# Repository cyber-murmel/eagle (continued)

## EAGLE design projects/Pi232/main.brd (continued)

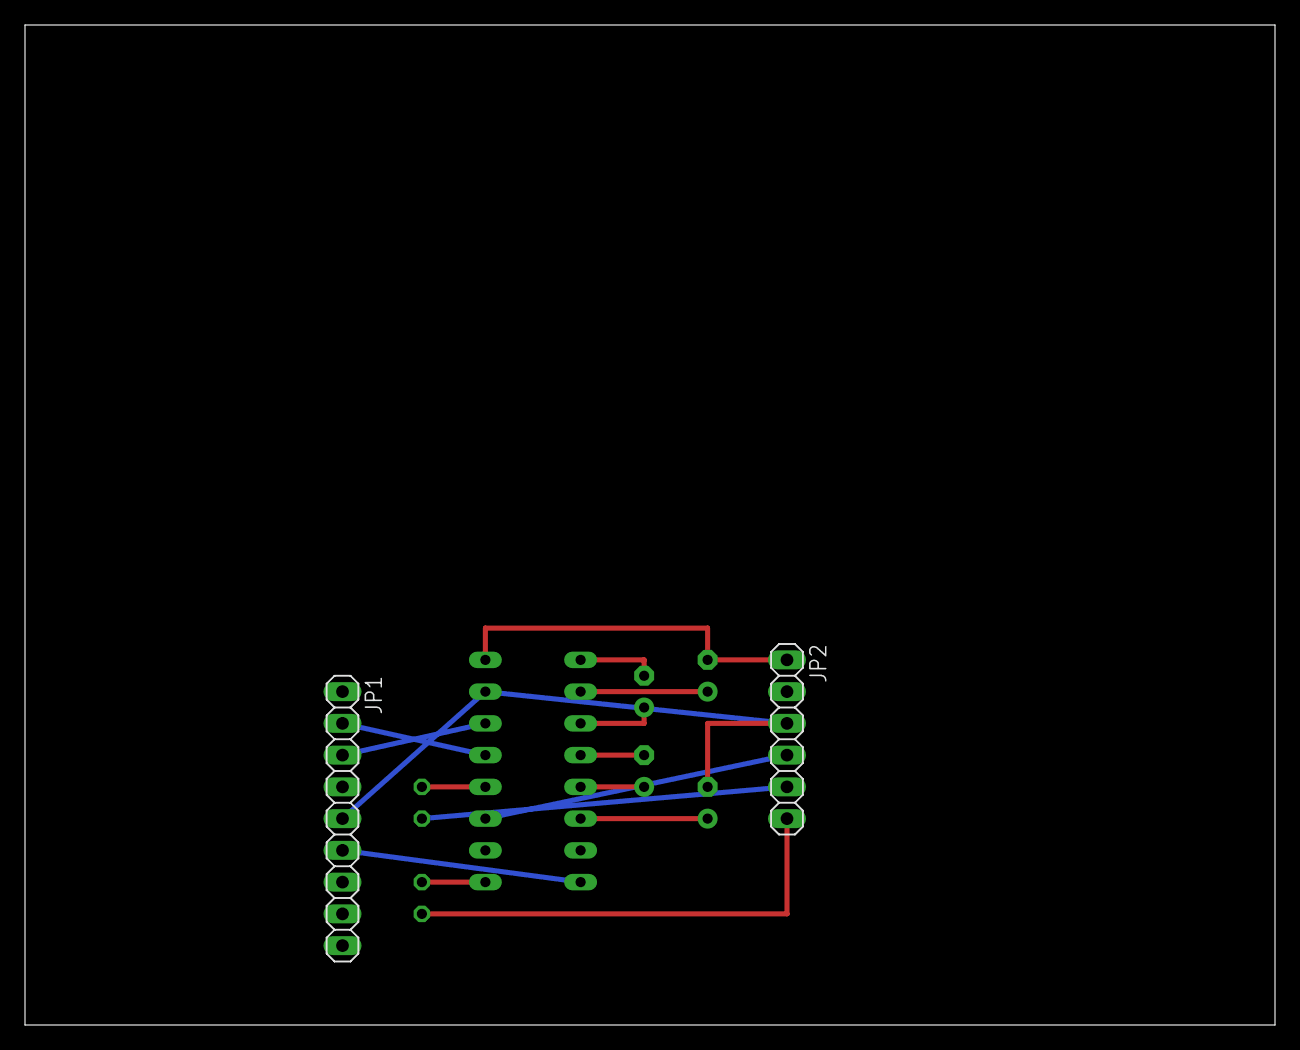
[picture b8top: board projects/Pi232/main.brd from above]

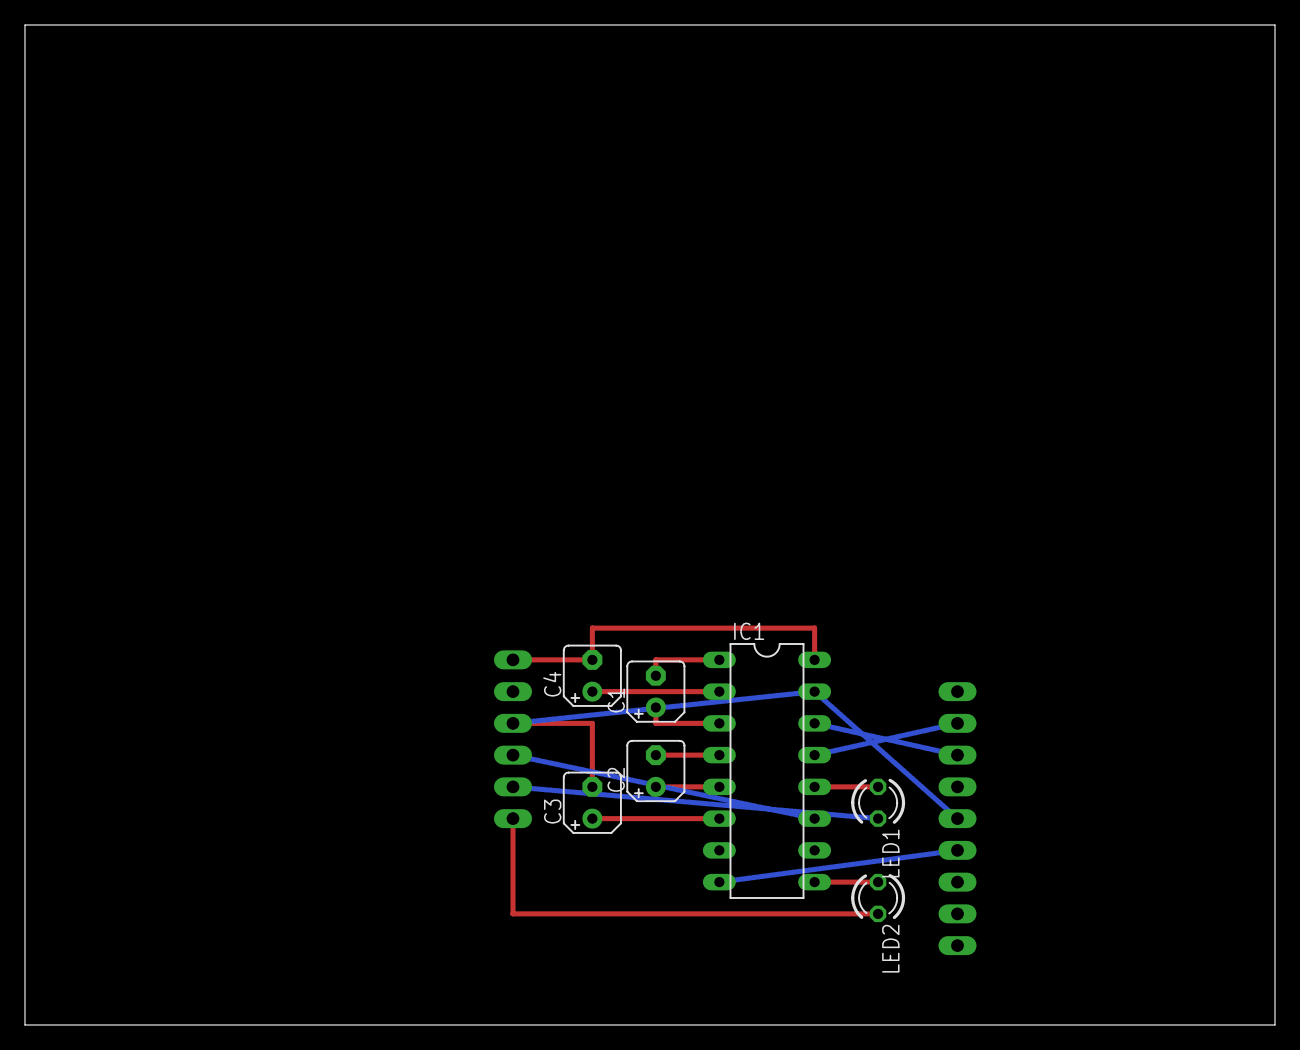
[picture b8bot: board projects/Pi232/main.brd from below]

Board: 2 copper layers, 100.0 x 80.0 mm, 9 parts (7 on the bottom side), 16 nets.

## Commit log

2017-01-16 add projects
2017-01-16 removed temporary files
2017-01-16 added gitignore
2017-01-16 renamed folder
2017-01-16 added coordinates
2017-01-16 corrected coordinates
2017-01-16 added dirty cheap PCB dru and cam
2017-01-16 bigger vias
2017-01-16 added Elecrow dru and cam
2017-01-16 added cam gerber output extension to ignore file
